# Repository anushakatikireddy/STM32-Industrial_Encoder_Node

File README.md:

# STM32-Industrial_Encoder_Node
Compact industrial encoder node designed for reliable position sensing and communication in robotics and motion control applications, developed as a complete hardware solution in KiCad.

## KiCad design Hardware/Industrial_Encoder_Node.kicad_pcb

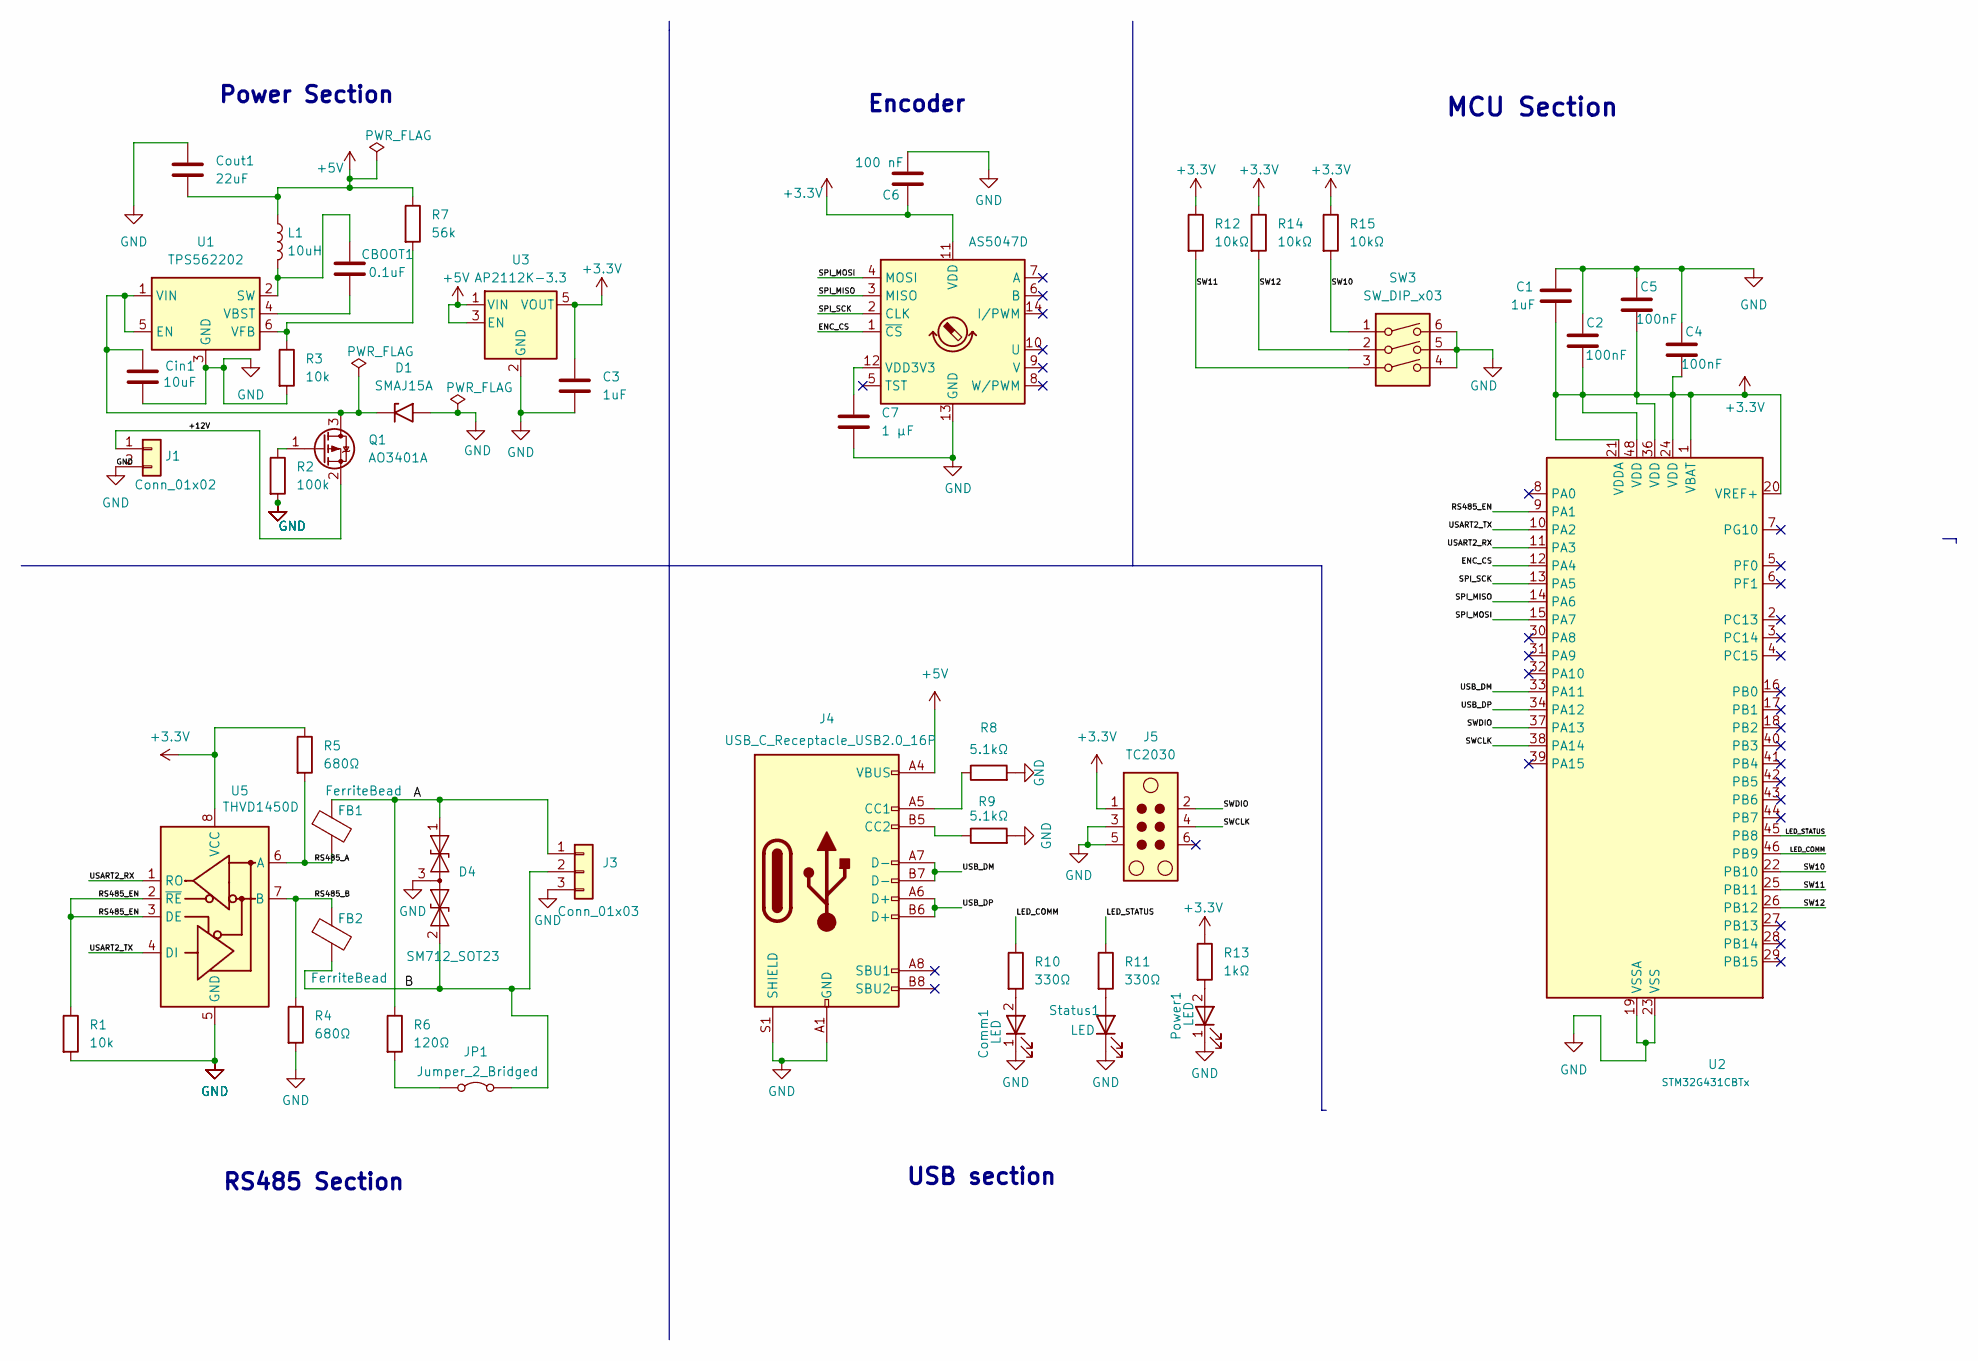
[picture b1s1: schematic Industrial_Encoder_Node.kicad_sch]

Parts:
C1, C3: 1uF; C_0603_1608Metric
C2, C4, C5: 100nF; C_0603_1608Metric
C6: 100 nF; C_0603_1608Metric
C7: 1 µF; C_0603_1608Metric
CBOOT1: 0.1uF; C_0603_1608Metric_Pad1.08x0.95mm_HandSolder
Cin1: 10uF; C_0805_2012Metric_Pad1.18x1.45mm_HandSolder
Comm1: LED; LED_0603_1608Metric
Cout1: 22uF; C_1206_3216Metric_Pad1.33x1.80mm_HandSolder
D1: SMAJ15A; D_SMA
D4: SM712_SOT23; SOT-23
FB1, FB2: FerriteBead; L_0603_1608Metric_Pad1.05x0.95mm_HandSolder
J1: Conn_01x02; TerminalBlock_Phoenix_PTSM-0,5-2-2.5-V-THR_1x02_P2.50mm_Ver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
J3: Conn_01x03; PhoenixContact_MSTBVA_2,5_3-G_1x03_P5.00mm_Vertical
J4: USB_C_Receptacle_USB2.0_16P; USB_C_Receptacle_GCT_USB4105-xx-A_16P_TopMnt_Horizontal
J5: TC2030; Tag-Connect_TC2030-IDC-NL_2x03_P1.27mm_Vertical
JP1: Jumper_2_Bridged; PinHeader_1x02_P2.54mm_Vertical
L1: 10uH; L_Bourns_SRN6045TA
Power1: LED; LED_0603_1608Metric_Pad1.05x0.95mm_HandSolder
Q1: AO3401A; SOT-23
R1, R3: 10k; R_0603_1608Metric_Pad0.98x0.95mm_HandSolder
R2: 100k; R_0603_1608Metric_Pad0.98x0.95mm_HandSolder
R4, R5: 680Ω; R_0603_1608Metric_Pad0.98x0.95mm_HandSolder
R6: 120Ω; R_0603_1608Metric_Pad0.98x0.95mm_HandSolder
R7: 56k; R_0603_1608Metric_Pad0.98x0.95mm_HandSolder
R8, R9: 5.1kΩ; R_0603_1608Metric_Pad0.98x0.95mm_HandSolder
R10, R11: 330Ω; R_0603_1608Metric_Pad0.98x0.95mm_HandSolder
R12, R14, R15: 10kΩ; R_0603_1608Metric_Pad0.98x0.95mm_HandSolder
R13: 1kΩ; R_0603_1608Metric_Pad0.98x0.95mm_HandSolder
SW3: SW_DIP_x03; SW_DIP_SPSTx03_Slide_6.7x9.18mm_W6.73mm_P2.54mm_LowProfile_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
Status1: LED; LED_0603_1608Metric_Pad1.05x0.95mm_HandSolder
U1: TPS562202; SOT-563
U2: STM32G431CBTx; LQFP-48_7x7mm_P0.5mm
U3: AP2112K-3.3; SOT-23-5
U4: AS5047D; TSSOP-14_4.4x5mm_P0.65mm
U5: THVD1450D; SOIC-8_3.9x4.9mm_P1.27mm

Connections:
+3.3V: C1.2, C2.2, C3.1, C4.2, C5.2, C6.1, J5.1, R5.1, R12.1, R13.1, R14.1, R15.1, U2.1 (VBAT), U2.20 (VREF+), U2.21 (VDDA), U2.24 (VDD), U2.36 (VDD), U2.48 (VDD), U3.5 (VOUT), U4.11 (VDD), U5.8 (VCC)
+5V: Cout1.2, J4.A4 (VBUS), J4.A9 (VBUS), J4.B4 (VBUS), J4.B9 (VBUS), L1.1, R7.1, U3.1 (VIN), U3.3 (EN)
/+12V: J1.1, Q1.2 (S)
/A: D4.1 (A1), FB1.1, J3.1, R6.1
/B: D4.2 (A2), FB2.2, J3.2, JP1.2 (B)
/ENC_CS: U2.12 (PA4), U4.1 (~CS)
/LED_COMM: R10.1, U2.46 (PB9)
/LED_STATUS: R11.1, U2.45 (PB8)
/RS485_A: FB1.2, R5.2, U5.6 (A)
/RS485_B: FB2.1, R4.1, U5.7 (B)
/RS485_EN: R1.1, U2.9 (PA1), U5.2 (~RE), U5.3 (DE)
/SPI_MISO: U2.14 (PA6), U4.3 (MISO)
/SPI_MOSI: U2.15 (PA7), U4.4 (MOSI)
/SPI_SCK: U2.13 (PA5), U4.2 (CLK)
/SW10: R15.2, SW3.1, U2.22 (PB10)
/SW11: R12.2, SW3.3, U2.25 (PB11)
/SW12: R14.2, SW3.2, U2.26 (PB12)
/SWCLK: J5.4, U2.38 (PA14)
/SWDIO: J5.2, U2.37 (PA13)
/USART2_RX: U2.11 (PA3), U5.1 (RO)
/USART2_TX: U2.10 (PA2), U5.4 (DI)
/USB_DM: J4.A7 (D-), J4.B7 (D-), U2.33 (PA11)
/USB_DP: J4.A6 (D+), J4.B6 (D+), U2.34 (PA12)
GND: C1.1, C2.1, C3.2, C4.1, C5.1, C6.2, C7.2, Cin1.2, Comm1.1 (K), Cout1.1, D1.2 (A2), D4.3 (common), J1.2, J3.3, J4.A1 (GND), J4.A12 (GND), J4.B1 (GND), J4.B12 (GND), J4.S1 (SHIELD), J5.3, J5.5, Power1.1 (K), R1.2, R2.2, R3.2, R4.2, R8.2, R9.2, SW3.4, SW3.5, SW3.6, Status1.1 (K), U1.3 (GND), U2.19 (VSSA), U2.23 (VSS), U2.35 (VSS), U2.47 (VSS), U3.2 (GND), U4.13 (GND), U5.5 (GND)
unnamed: Comm1.2 (A), R10.2
unnamed: Cin1.1, D1.1 (A1), Q1.3 (D), U1.1 (VIN), U1.5 (EN)
unnamed: J4.A5 (CC1), R8.1
unnamed: J4.B5 (CC2), R9.1
unnamed: JP1.1 (A), R6.2
unnamed: Power1.2 (A), R13.2
unnamed: Q1.1 (G), R2.1
unnamed: R11.2, Status1.2 (A)
unnamed: CBOOT1.1, L1.2, U1.2 (SW)
unnamed: CBOOT1.2, U1.4 (VBST)
unnamed: R3.1, R7.2, U1.6 (VFB)
unnamed: C7.1, U4.12 (VDD3V3)

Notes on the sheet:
Power Section
RS485 Section
MCU Section
Encoder
USB section

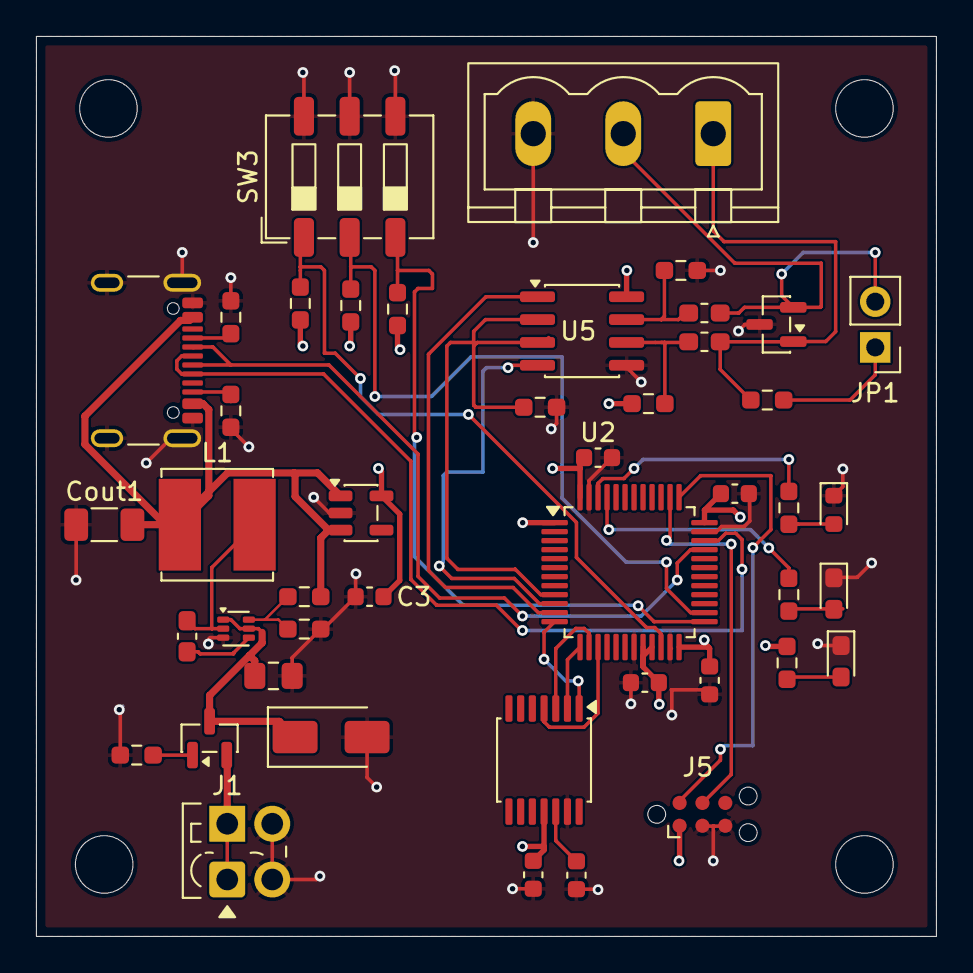
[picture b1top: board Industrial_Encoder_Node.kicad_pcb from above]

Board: 4 copper layers, 50.0 x 50.0 mm, 45 parts (0 on the bottom side), 36 nets.

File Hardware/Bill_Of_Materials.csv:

No,Reference,Qty,Value,Footprint,Component
1,"C1, C3",2,1uF,0603,"Ceramic capacitor, 10V+"
2,"C2, C4, C5",3,100nF,0603,"Ceramic capacitor, 10V+"
3,C6,1,100nF,0603,"Ceramic capacitor, 10V+"
4,C7,1,1uF,0603,"Ceramic capacitor, 10V+"
5,CBOOT1,1,0.1uF,0603,"Ceramic capacitor, 10V+"
6,Cin1,1,10uF,0805,"Ceramic capacitor, 25V+"
7,Comm1,1,LED,0603,Blue SMD LED
8,Cout1,1,22uF,1206,"Ceramic capacitor, 10V+"
9,D1,1,SMAJ15A,SMA,"15V TVS diode, 400W peak"
10,D4,1,SM712,SOT-23,RS485/USB TVS diode array
11,"FB1, FB2",2,Ferrite Bead,0603,"~600 Ohm @100MHz, 500mA"
12,J1,1,2-pin terminal,PTSM 2.5mm,"Phoenix PTSM-0,5-2-2.5-V-THR"
13,J3,1,3-pin terminal,MSTB 5mm,"Phoenix MSTBVA 2,5/3-G"
14,J4,1,USB-C 16P,USB4105,"GCT USB-C 2.0 receptacle, horizontal"
15,J5,1,TC2030,Tag-Connect,"TC2030-IDC-NL (no-leg, not soldered)"
16,JP1,1,Jumper 2-pin,2.54mm header,RS485 termination enable
17,L1,1,10uH,SRN6045,"Bourns shielded power inductor, 2A+"
18,"Power1, Status1",2,LED,0603,Green + Amber SMD LEDs
19,Q1,1,AO3401A,SOT-23,"P-ch MOSFET, -30V, -4A"
20,"R1, R3",2,10kOhm,0603,1% resistor
21,R2,1,100kOhm,0603,1% resistor (see warning in Section 4.4)
22,"R4, R5",2,680Ohm,0603,1% resistor
23,R6,1,120Ohm,0603,"1% resistor, RS485 termination"
24,R7,1,56kOhm,0603,"1% resistor, bus bias"
25,"R8, R9",2,5.1kOhm,0603,"1% resistor, USB-C CC pull-down"
26,"R10, R11",2,330Ohm,0603,LED current limiting
27,"R12, R14, R15",3,10kOhm,0603,"1% resistor, pull-ups"
28,R13,1,1kOhm,0603,LED current limiting
29,SW3,1,DIP-3 switch,SMD slide,"3-position DIP switch, node address"
30,U1,1,TPS562202,SOT-563,TI 2A sync buck converter
31,U2,1,STM32G431CBT6,LQFP-48,"ST Cortex-M4 MCU, 128KB Flash"
32,U3,1,AP2112K-3.3,SOT-23-5,Diodes Inc. 600mA LDO
33,U4,1,AS5047D,TSSOP-14,ams 14-bit magnetic encoder
34,U5,1,THVD1450D,SOIC-8,TI 20Mbps RS485 transceiver
